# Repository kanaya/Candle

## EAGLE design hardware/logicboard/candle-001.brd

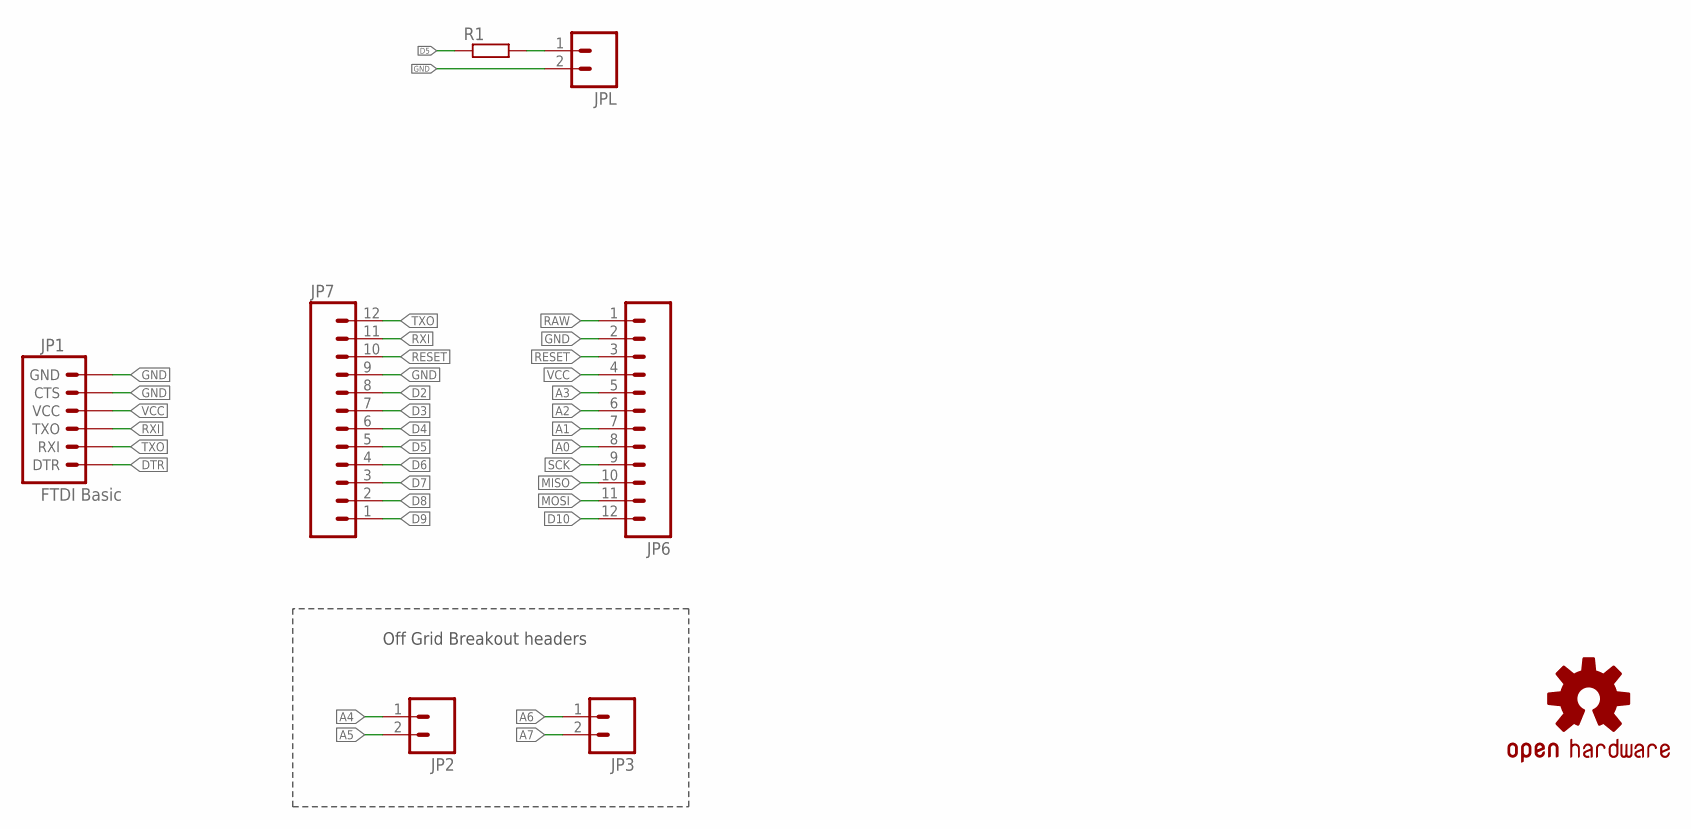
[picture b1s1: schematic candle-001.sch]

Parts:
JP1: FTDI Basic; 1X06
JP2, JP3: M02PTH; 1X02
JP6, JP7: M12PTH; 1X12
JPL: M02PTH; 1X02
R1: R-EU_0204/5; 0204/5
U$3: OSHW-LOGOS; OSHW-LOGO-S

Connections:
A0: JP6.8
A1: JP6.7
A2: JP6.6
A3: JP6.5
A4: JP2.1
A5: JP2.2
A6: JP3.1
A7: JP3.2
D2: JP7.8
D3: JP7.7
D4: JP7.6
D5: JP7.5, R1.1
D6: JP7.4
D7: JP7.3
D8: JP7.2
D9: JP7.1
D10: JP6.12
DTR: JP1.1 (DTR)
GND: JP1.5 (CTS), JP1.6 (GND), JP6.2, JP7.9, JPL.2
MISO: JP6.10
MOSI: JP6.11
unnamed: JPL.1, R1.2
RAW: JP6.1
RESET: JP6.3, JP7.10
RXI: JP1.3 (TXO), JP7.11
SCK: JP6.9
TXO: JP1.2 (RXI), JP7.12
VCC: JP1.4 (VCC), JP6.4

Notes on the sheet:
Off Grid Breakout headers

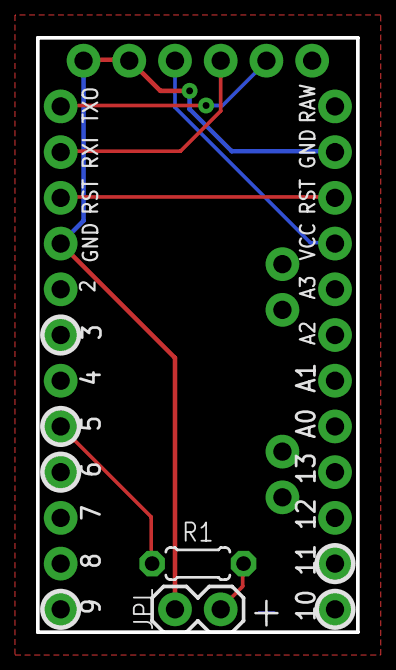
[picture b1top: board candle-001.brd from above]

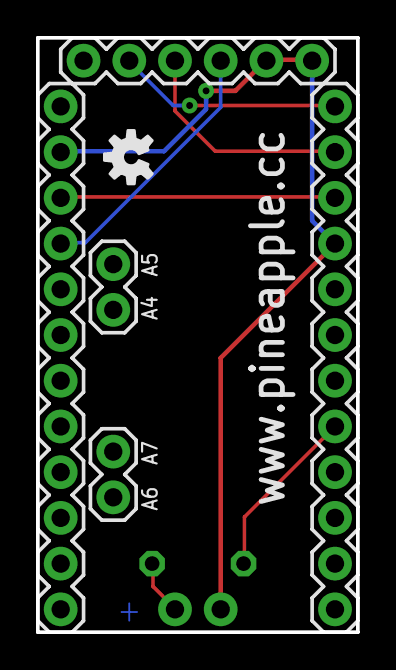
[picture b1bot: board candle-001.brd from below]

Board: 2 copper layers, 17.8 x 33.0 mm, 8 parts (6 on the bottom side), 7 nets.

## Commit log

2020-08-24 Initial commit. (Imported Eagle files of Pro Mini.)
2020-08-24 First try.
2020-08-24 Added gitignore.
